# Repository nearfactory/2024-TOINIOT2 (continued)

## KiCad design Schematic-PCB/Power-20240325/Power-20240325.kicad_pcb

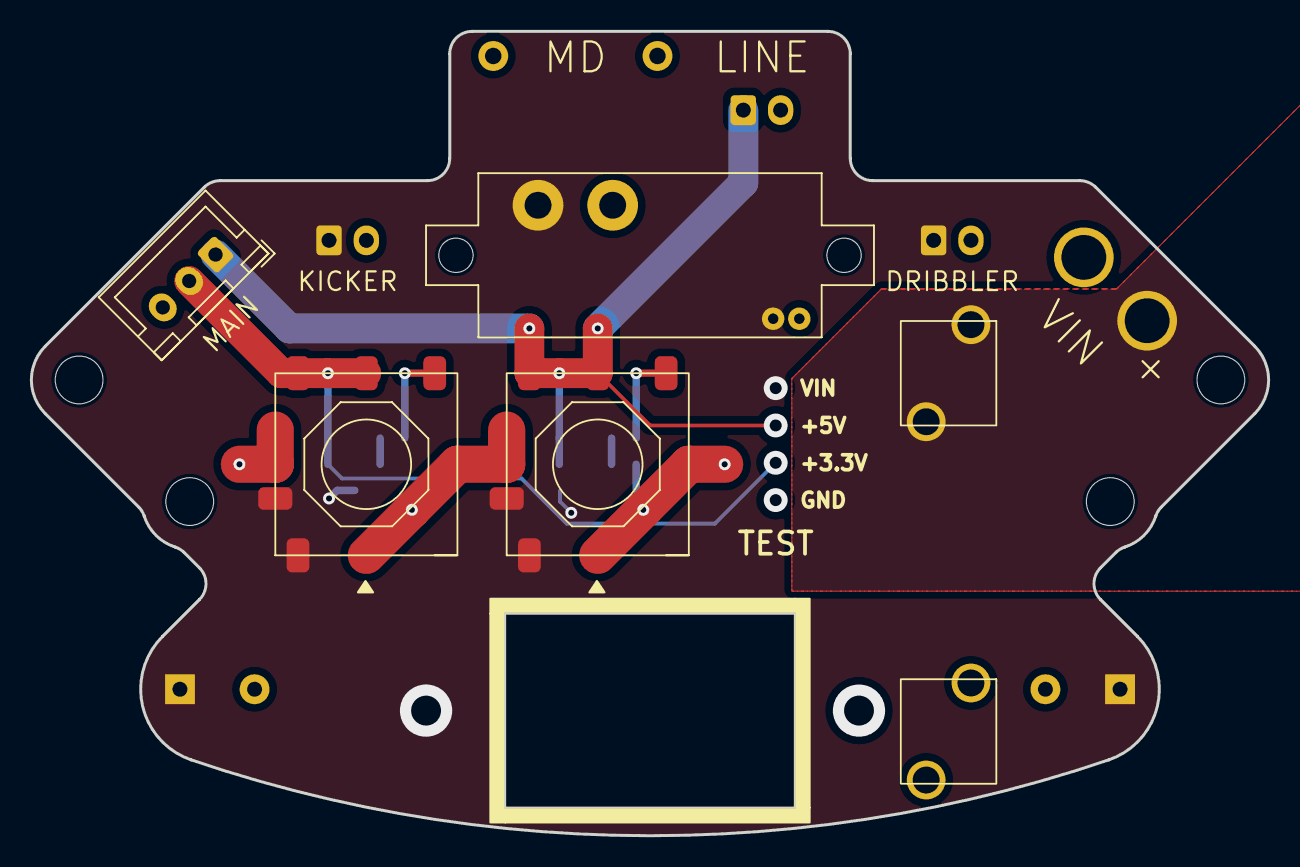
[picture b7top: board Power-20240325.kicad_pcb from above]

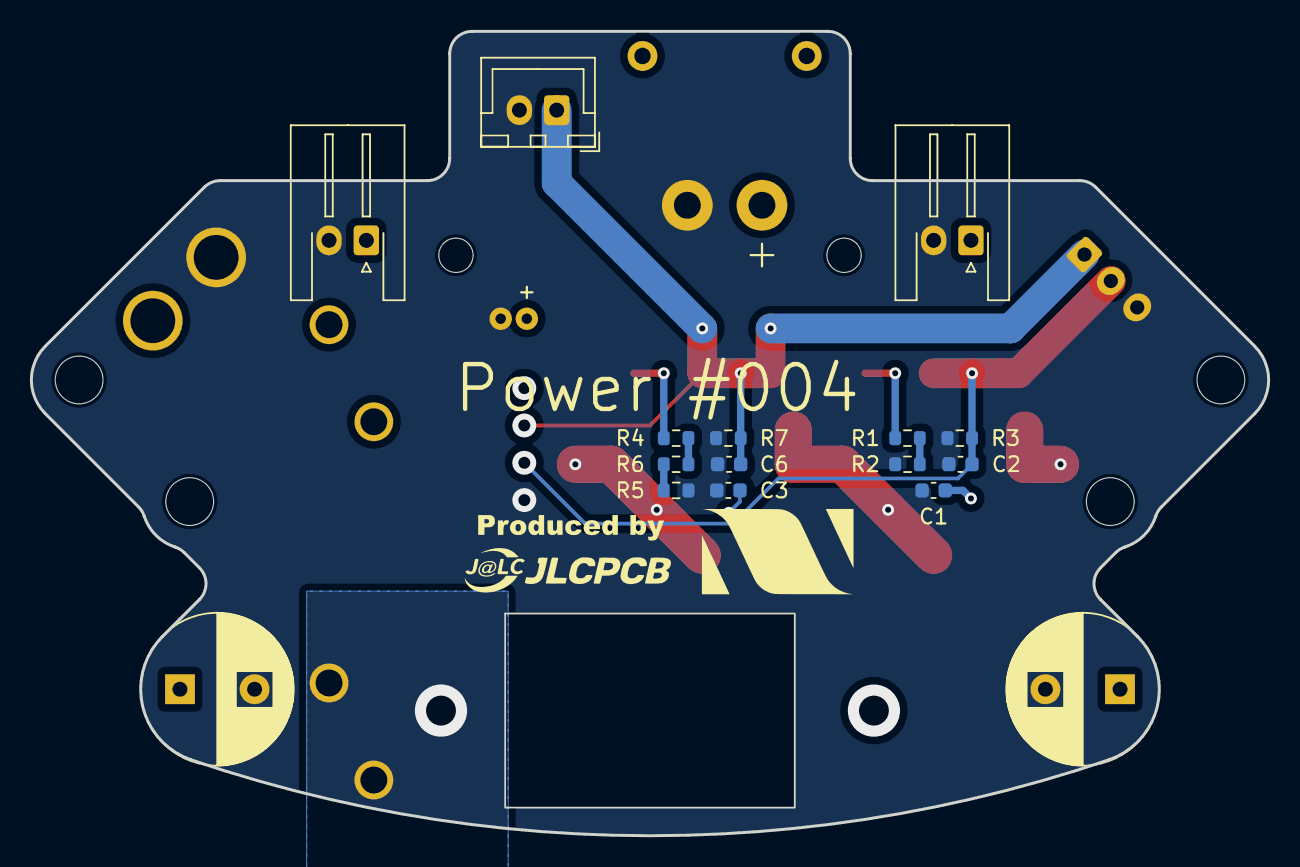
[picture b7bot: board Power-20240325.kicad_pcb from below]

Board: 2 copper layers, 82.9 x 53.9 mm, 24 parts (17 on the bottom side), 10 nets.

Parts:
+: Voltmeter_DC; VoltMeter
C1, C3: 22uF; C_0603_1608Metric
C2, C6: 10uF; C_0603_1608Metric
C4, C5: 1000uF; CP_Radial_D10.0mm_P5.00mm
F1: 10A/15A; Fuse
J3: Conn_01x02_Pin; JST_XH_B2B-XH-A_1x02_P2.50mm_Vertical
J6: Conn_01x02_Pin; XT30PW-M
J6#2: Conn_01x02_Pin; JST_XH_S2B-XH-A-1_1x02_P2.50mm_Horizontal
KICKER: Conn_01x02_Pin; JST_XH_S2B-XH-A-1_1x02_P2.50mm_Horizontal
MAIN: Conn_01x03_Pin; JST_XH_B3B-XH-A_1x03_P2.50mm_Vertical
R1: 1.5K; R_0603_1608Metric
R2: 680; R_0603_1608Metric
R3, R7: 1.2K; R_0603_1608Metric
R4: 1K; R_0603_1608Metric
R5: 10; R_0603_1608Metric
R6: 330; R_0603_1608Metric
SW1: SW_DPST_x2; RA1113112R
U1, U2: OKL-T6-W12N-C
VIN: Conn_01x02_Pin; VIN

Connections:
+3.3V: C2.1, MAIN.2, R3.1, U1.4 (Vout), U1.5 (Sense)
+5V: C6.1, J3.1, MAIN.1, R7.1, U2.4 (Vout), U2.5 (Sense)
GND: +.1 (-), C1.2, C2.2, C3.2, C4.2, C5.2, C6.2, J3.2, J6.2, J6#2.2, KICKER.2, MAIN.3, R2.2, R3.2, R5.1, R7.2, U1.1 (ON/OFF), U1.3 (GND), U1.7 (GND), U2.1 (ON/OFF), U2.3 (GND), U2.7 (GND), VIN.2
unnamed: F1.1, VIN.1
unnamed: R1.2, R2.1
unnamed: R4.2, R6.1
unnamed: R5.2, R6.2
unnamed: R1.1, U1.6 (Trim)
unnamed: R4.1, U2.6 (Trim)
VIN: +.2 (+), C1.1, C3.1, C4.1, C5.1, J6.1, J6#2.1, KICKER.1, U1.2 (Vin), U2.2 (Vin)

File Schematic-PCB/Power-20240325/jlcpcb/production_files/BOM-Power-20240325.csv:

Comment,Designator,Footprint,LCSC
1K,R4,R_0603_1608Metric,C21190
1.2K,"R3,R7",R_0603_1608Metric,C22765
1.5K,R1,R_0603_1608Metric,C22843
10,R5,R_0603_1608Metric,C22859
330,R6,R_0603_1608Metric,C23138
680,R2,R_0603_1608Metric,C23228
22uF,"C1,C3",C_0603_1608Metric,C45783
10uF,"C2,C6",C_0603_1608Metric,C96446
Conn_01x02_Pin,J6,JST_XH_S2B-XH-A-1_1x02_P2.50mm_Horizontal,

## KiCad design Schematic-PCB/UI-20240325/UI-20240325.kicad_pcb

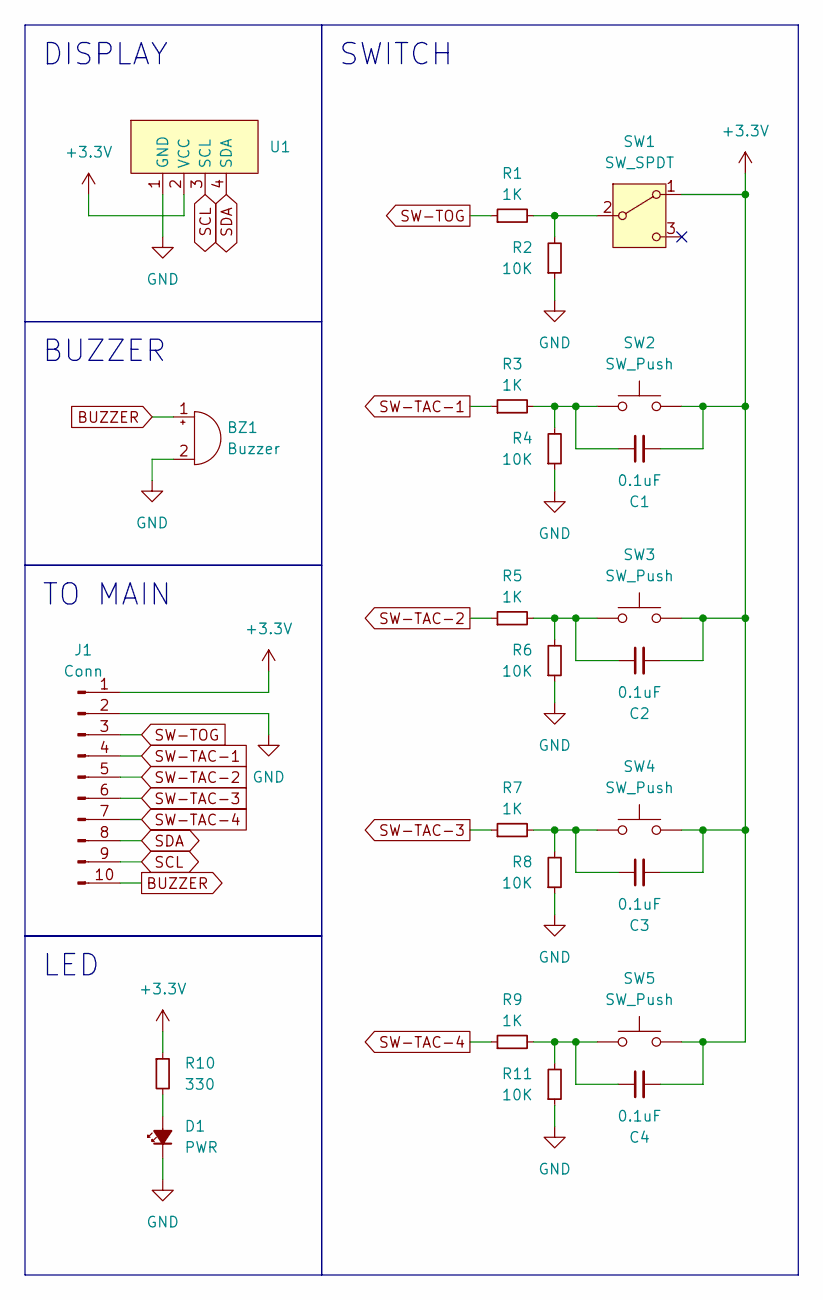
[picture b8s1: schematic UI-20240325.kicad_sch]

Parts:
BZ1: Buzzer; PKM13EPYH4000-A0
C1, C2, C3, C4: 0.1uF; C_0603_1608Metric
D1: PWR; LED_0603_1608Metric
J1: Conn; JST_XH_B10B-XH-A_1x10_P2.50mm_Vertical
R1, R3, R5, R7, R9: 1K; R_0603_1608Metric
R2, R4, R6, R8, R11: 10K; R_0603_1608Metric
R10: 330; R_0603_1608Metric
SW1: SW_SPDT; 2MS1-T1-B4-VS2-Q-E-S
SW2, SW3, SW4, SW5: SW_Push; TVBP06-B043C
U1: Display

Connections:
+3.3V: C1.2, C2.2, C3.2, C4.2, J1.1, R10.1, SW1.1 (A), SW2.2, SW3.2, SW4.2, SW5.2, U1.2 (VCC)
BUZZER: BZ1.1 (+), J1.10
GND: BZ1.2 (-), D1.1 (K), J1.2, R2.1, R4.1, R6.1, R8.1, R11.1, U1.1 (GND)
unnamed: C1.1, R3.2, R4.2, SW2.1
unnamed: C2.1, R5.2, R6.2, SW3.1
unnamed: C3.1, R7.2, R8.2, SW4.1
unnamed: C4.1, R9.2, R11.2, SW5.1
unnamed: D1.2 (A), R10.2
unnamed: R1.2, R2.2, SW1.2 (B)
SCL: J1.9, U1.3 (SCL)
SDA: J1.8, U1.4 (SDA)
SW-TAC-1: J1.4, R3.1
SW-TAC-2: J1.5, R5.1
SW-TAC-3: J1.6, R7.1
SW-TAC-4: J1.7, R9.1
SW-TOG: J1.3, R1.1

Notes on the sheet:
DISPLAY
BUZZER
TO MAIN
SWITCH
LED

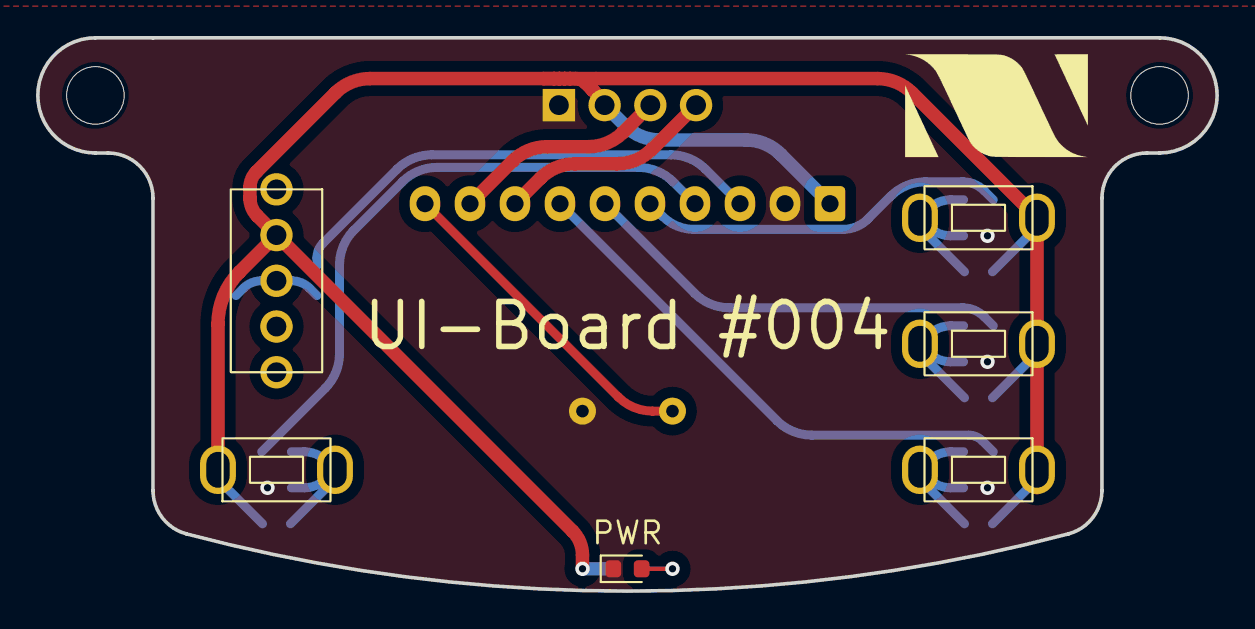
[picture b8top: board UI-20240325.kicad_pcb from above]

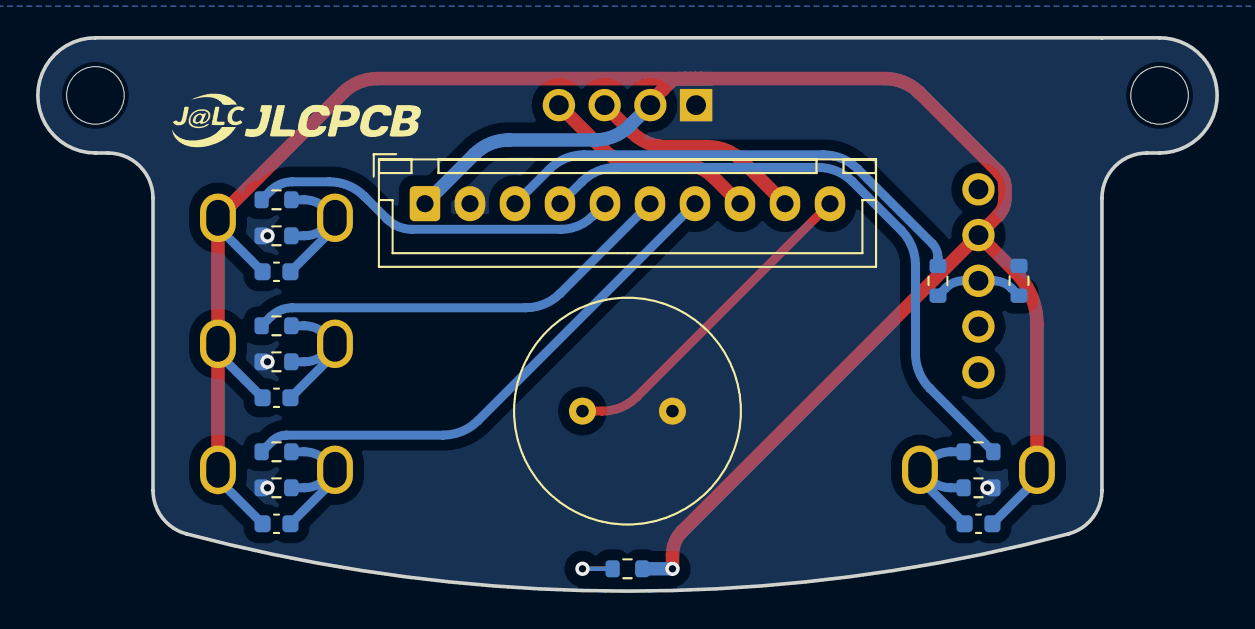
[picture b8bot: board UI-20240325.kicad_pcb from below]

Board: 2 copper layers, 65.5 x 30.7 mm, 24 parts (17 on the bottom side), 16 nets.

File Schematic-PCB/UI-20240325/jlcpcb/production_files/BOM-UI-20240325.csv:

Comment,Designator,Footprint,LCSC
0.1uF,"C1,C2,C3,C4",C_0603_1608Metric,C14663
1K,"R1,R3,R5,R7,R9",R_0603_1608Metric,C21190
330,R10,R_0603_1608Metric,C23138
10K,"R11,R2,R4,R6,R8",R_0603_1608Metric,C25804
